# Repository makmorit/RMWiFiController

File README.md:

# RMWiFiController

## 概要

鉄道模型のレイアウト上（または近く）に配置したコントローラーを、手元のリモコンで操作する装置です。

## 構成

大きく分けるとパワーコントローラー部、リモコン部からなります。

これらに、Wi-Fiモジュールをそれぞれ搭載させ、制御データを同期させています。

基本的に内部機能は同一なので、コードは共用してます。

### コントローラー基板

リモコンからのリモート制御用信号を、Wi-Fiモジュール（Arduino）で受けます。

PICマイコン（PIC16F18857。以下同）で、指定されたDuty比をもとにPWM信号を生成し、パワーMOSFETをドライブして駆動電圧を生成してます。

Duty比はリモコン基板でも、コントローラー基板上のつまみでも、どちらでも調整が可能です。

### リモコン基板

リモコン基板上のつまみで、Duty比を調整し、Wi-Fiモジュール（Arduino）からコントローラー基板へ送信します。

ただし、コントローラー基板と同じファームを使用しているので、ここでもPWM信号が生成され、その電圧でLEDを点灯させています（すなわちDuty比の大小でLEDが明るくなったり暗くなったりします）。

## 回路

EAGLE で作成したものを公開しております。

まだ、実体配線図は作成途上ですが、回路図はブレッドボードの実験回路にて動作を確認済みです。

## 機能

2017/04/22現在、機能を再編成中です。

現在は下記機能のみの提供となります。

(1) 基板上のつまみ（ロータリーエンコーダー）で、フィーダーから供給する動力電圧を制御

(2) 基板上のボタン（タクトスイッチ）で、フィーダーの極性（正転／反転）を切替え

### 将来追加予定の機能

(1) ボタン運転 - 基板上に用意した専用ボタンを押すたびに、加速（-->あらかじめ決めておいた最高動力で定速走行）-->減速（-->あらかじめ決めておいた停止ぎりぎりの動力で徐行）-->停止、の流れで運転することができる機能です。

(2) ダイヤ運転 - あらかじめ用意した運転条件／運転間隔で、ボタン運転と同じ流れの運転が実行できる機能です。

(3) 条件設定 - 上記ボタン運転／ダイヤ運転の条件（諸々のパラメーター）を、液晶ディスプレイをみながら設定／変更できる機能です。

## タッチセンサーの配線レス化

TOMIXタッチセンサーから、コントローラーの配線を無線化して、レイアウト全体の配線を極限まで簡素化するプランがあります。

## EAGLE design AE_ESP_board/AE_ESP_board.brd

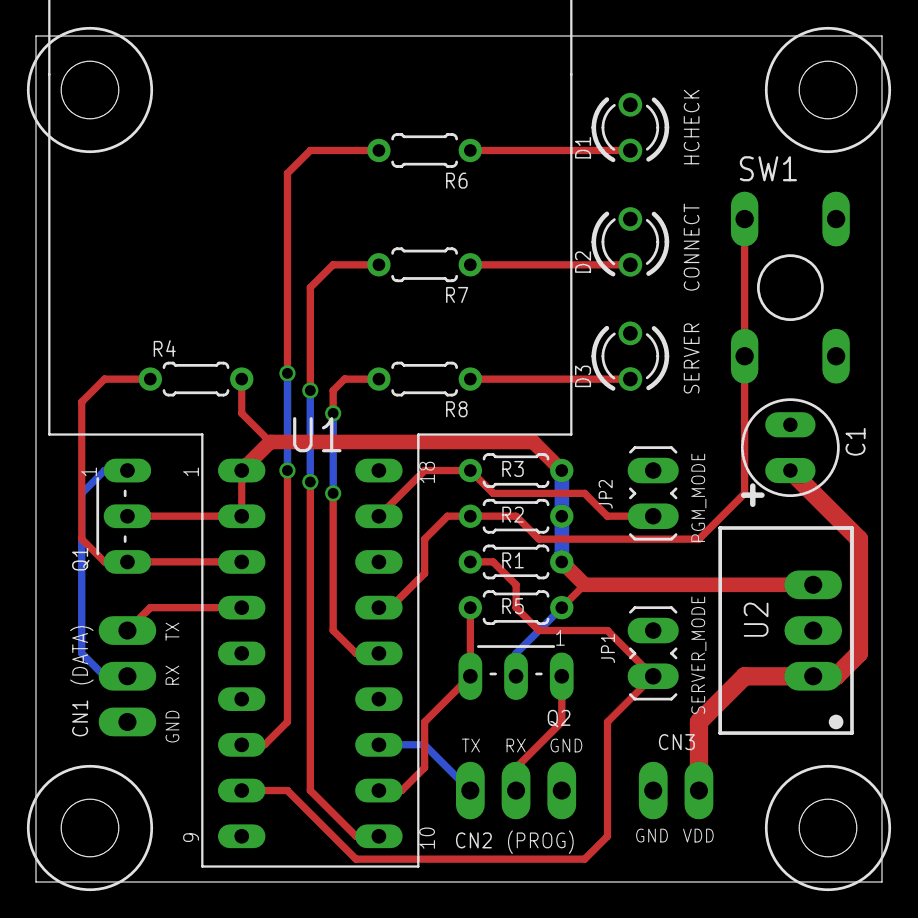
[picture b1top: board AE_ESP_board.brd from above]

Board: 2 copper layers, 47.0 x 47.0 mm, 26 parts (0 on the bottom side), 18 nets.

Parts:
C1: 35V47uF; ELECAP_D5_100MIL
CN1: SW_UART_IF; UART_IF_3PIN
CN2: HW_UART_IF; UART_IF_3PIN
CN3: POWER_IF; HEADER_2PIN_POWER_IF
D1, D2, D3: LED_3MM; LED3MM
H1, H2, H3, H4: MOUNT_HOLE_3.2; 3,2
JP1: PGM_MODE; JP1
JP2: SERVER_MODE; JP1
Q1, Q2: 2N7000; TO-92NL
R1, R2, R3, R4, R5: 10k; RESISTOR_0204_200MIL
R6, R7, R8: 330; RESISTOR_0204_200MIL
SW1: 10-XX; B3F-10XX
U1: AE-ESP-WROOM-02; DIL18_AE-ESP-WROOM-02
U2: M78AR033-0.5; SIP3

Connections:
0V: C1.-, CN1.1, CN2.1, CN3.1, D1.K, D2.K, D3.K, JP1.1, JP2.2, SW1.2, SW1.4, U1.5, U1.6, U1.9, U1.13, U1.18, U2.2
+3V3: Q1.2, Q2.2, R1.2, R2.2, R3.2, R4.2, R5.2, U1.1, U1.2, U2.3
+12V: C1.+, CN3.2, U2.1
HW_UART_TXD: CN2.3, U1.12
LED_CONNECTING: R7.2, U1.10
LED_HCHECK: R6.2, U1.7
unnamed: CN1.3, U1.4
unnamed: JP2.1, R3.1, U1.17
unnamed: CN2.2, Q2.1
unnamed: R8.2, U1.14
unnamed: D3.A, R8.1
unnamed: Q2.3, R5.1, U1.11
unnamed: JP1.2, R1.1, U1.8
unnamed: R2.1, SW1.1, SW1.3, U1.15
unnamed: D2.A, R7.1
unnamed: D1.A, R6.1
SW_UART_RXD: CN1.2, Q1.1
SW_UART_RXD_IN: Q1.3, R4.1, U1.3

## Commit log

2017-03-02 PICマイコン用ファームウェアの初版
2017-03-02 Arduino用ファームウェアの初版
    RMWiFi.h へのシンボリックリンクが、各サブディレクトリー配下に別途必要になります。
2017-03-02 概要記述
2017-03-02 説明用画像
2017-03-02 概要更新
2017-03-03 EAGLE 部品ライブラリー初版登録
    データシートも為念で登録するようにします。
2017-03-04 PIC16F1938の部品データを追加
2017-04-06 ファイル整理
    共通利用ファイルを library_for_eagle リポジトリーに移動しました
2017-04-06 ファイルを整理
    不要ファイル削除
2017-04-09 固有部品の初版
2017-04-09 リモコン部の回路図初版
2017-04-10 リモコン部のファイル名称変更
2017-04-10 固有部品を追加
    フィーダー接続用端子
2017-04-10 パワーコントローラー部の回路図初版
2017-04-11 Arduino用ファームウェアを更新
    RMWiFi.hを各サブディレクトリー配下に配置しています。
    （リンクを不要とするため）
2017-04-12 Arduinoソースコードを再編成
    ・フォルダー／ファイル構成の見直し
    ・コメントの見直し
    ・ヘルスチェックリクエストを、ブラウザーなどから発行した場合、親機だけでなく子機でもヘルスチェック用LEDがOn/Offできるように修正
2017-04-19 Arduinoが不要になったため削除
    別途作成のWi-Fi HTTP通信基板に接続する前提
2017-04-19 Wi-Fi部が不要になったため回路図から削除
    別途作成のWi-Fi HTTP通信基板に接続する前提
2017-04-20 MODE_SELECT端子を新設
    ・PICのファームウェアを共通化する目的
    ・MODE_SELECT=LOWの場合は親機（パワーコントローラー部）
    ・MODE_SELECT=HIGHの場合は子機（リモコン部）
    ・ディレクトリー名を EAGLE —> ControllerBoardに改称
2017-04-20 Wi-Fi HTTP通信基板の回路図／ファームウェア初版
    ・Wi-Fi部（AE-ESP-WROOM-02）の回路／ファームウェアを再構築
    ・親機／子機で同じ回路／ファームウェアを使用するよう修正
2017-04-21 いったん機能削減してPICソースコードを再編成
2017-04-21 PICソースコードをさらに再編成
2017-04-21 再編成前のソースコードを削除
2017-04-27 [WIP] PIC16F18857用ソースコードの初版
    実機が未到着なので、動作確認できていません。
2017-04-28 設定の見直し
    ・タイマー２の設定をPIC16F18857/18877の仕様に整合させる
    ・タイマー０の設定が間違っていたため修正
    ・レジスター名称のコーディングを見直し
2017-04-28 コメントがまちがっているので修正
2017-05-16 定数を変更
    SSID／パスフレーズ／IPアドレスを、Wi-Fi HTTPサーバーに固有な内容へ変更
2017-05-16 Wi-Fiアクセスポイントモードでの試験用コード
    APモードのロジックを、WiFiServerProcessに移設した後、元に戻す予定です。
2017-05-17 Wi-Fiアクセスポイントモードに変更
    ・APモードのロジックを、WiFiServerProcessに移設
    ・コメントを修正
    ・アクセスポイント／HTTPサーバー起動後の待ち時間を調整
2017-05-18 コメントを修正
2017-06-15 ボードレイアウトを削除
    設計を全面的に見直しのため
2017-06-15 回路図を修正
    150mA —> 500mAのCMOSレギュレーターに変更
2017-06-16 PartsForProto.lbrをマージ
    こちらのPartsForProto.lbrは削除
2017-06-17 回路図を修正
2017-06-17 レイアウトを修正
2017-06-18 レイアウトを修正
    基板のサイズが間違っていたので修正
    LEDのキャプションを追加
2017-07-24 レイアウトの見直し
    レイアウトを47mm x 47mm に縮小します。
2017-07-25 レイアウトを大幅見直し
2017-07-26 レイアウト見直し
    LED以外はリード部品とする
2017-07-27 LEDを表面実装にする理由がないので、こちらもリード部品化 （ただし3mm砲弾型前提）
2017-07-28 配線を確定
2017-12-15 タッチセンサーの配線レス化についての記述を追加
2019-02-10 現状の姿
2019-02-10 回路図を作成
    ・まだフレームだけです
